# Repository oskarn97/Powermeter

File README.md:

# Powermeter
8-phase induction power meter 16A / 230V

In order to measure the power consumption in each of my rooms, I've designed this induction-based 8 phase power meter, that can be installed in your electricity box next to your breakers.

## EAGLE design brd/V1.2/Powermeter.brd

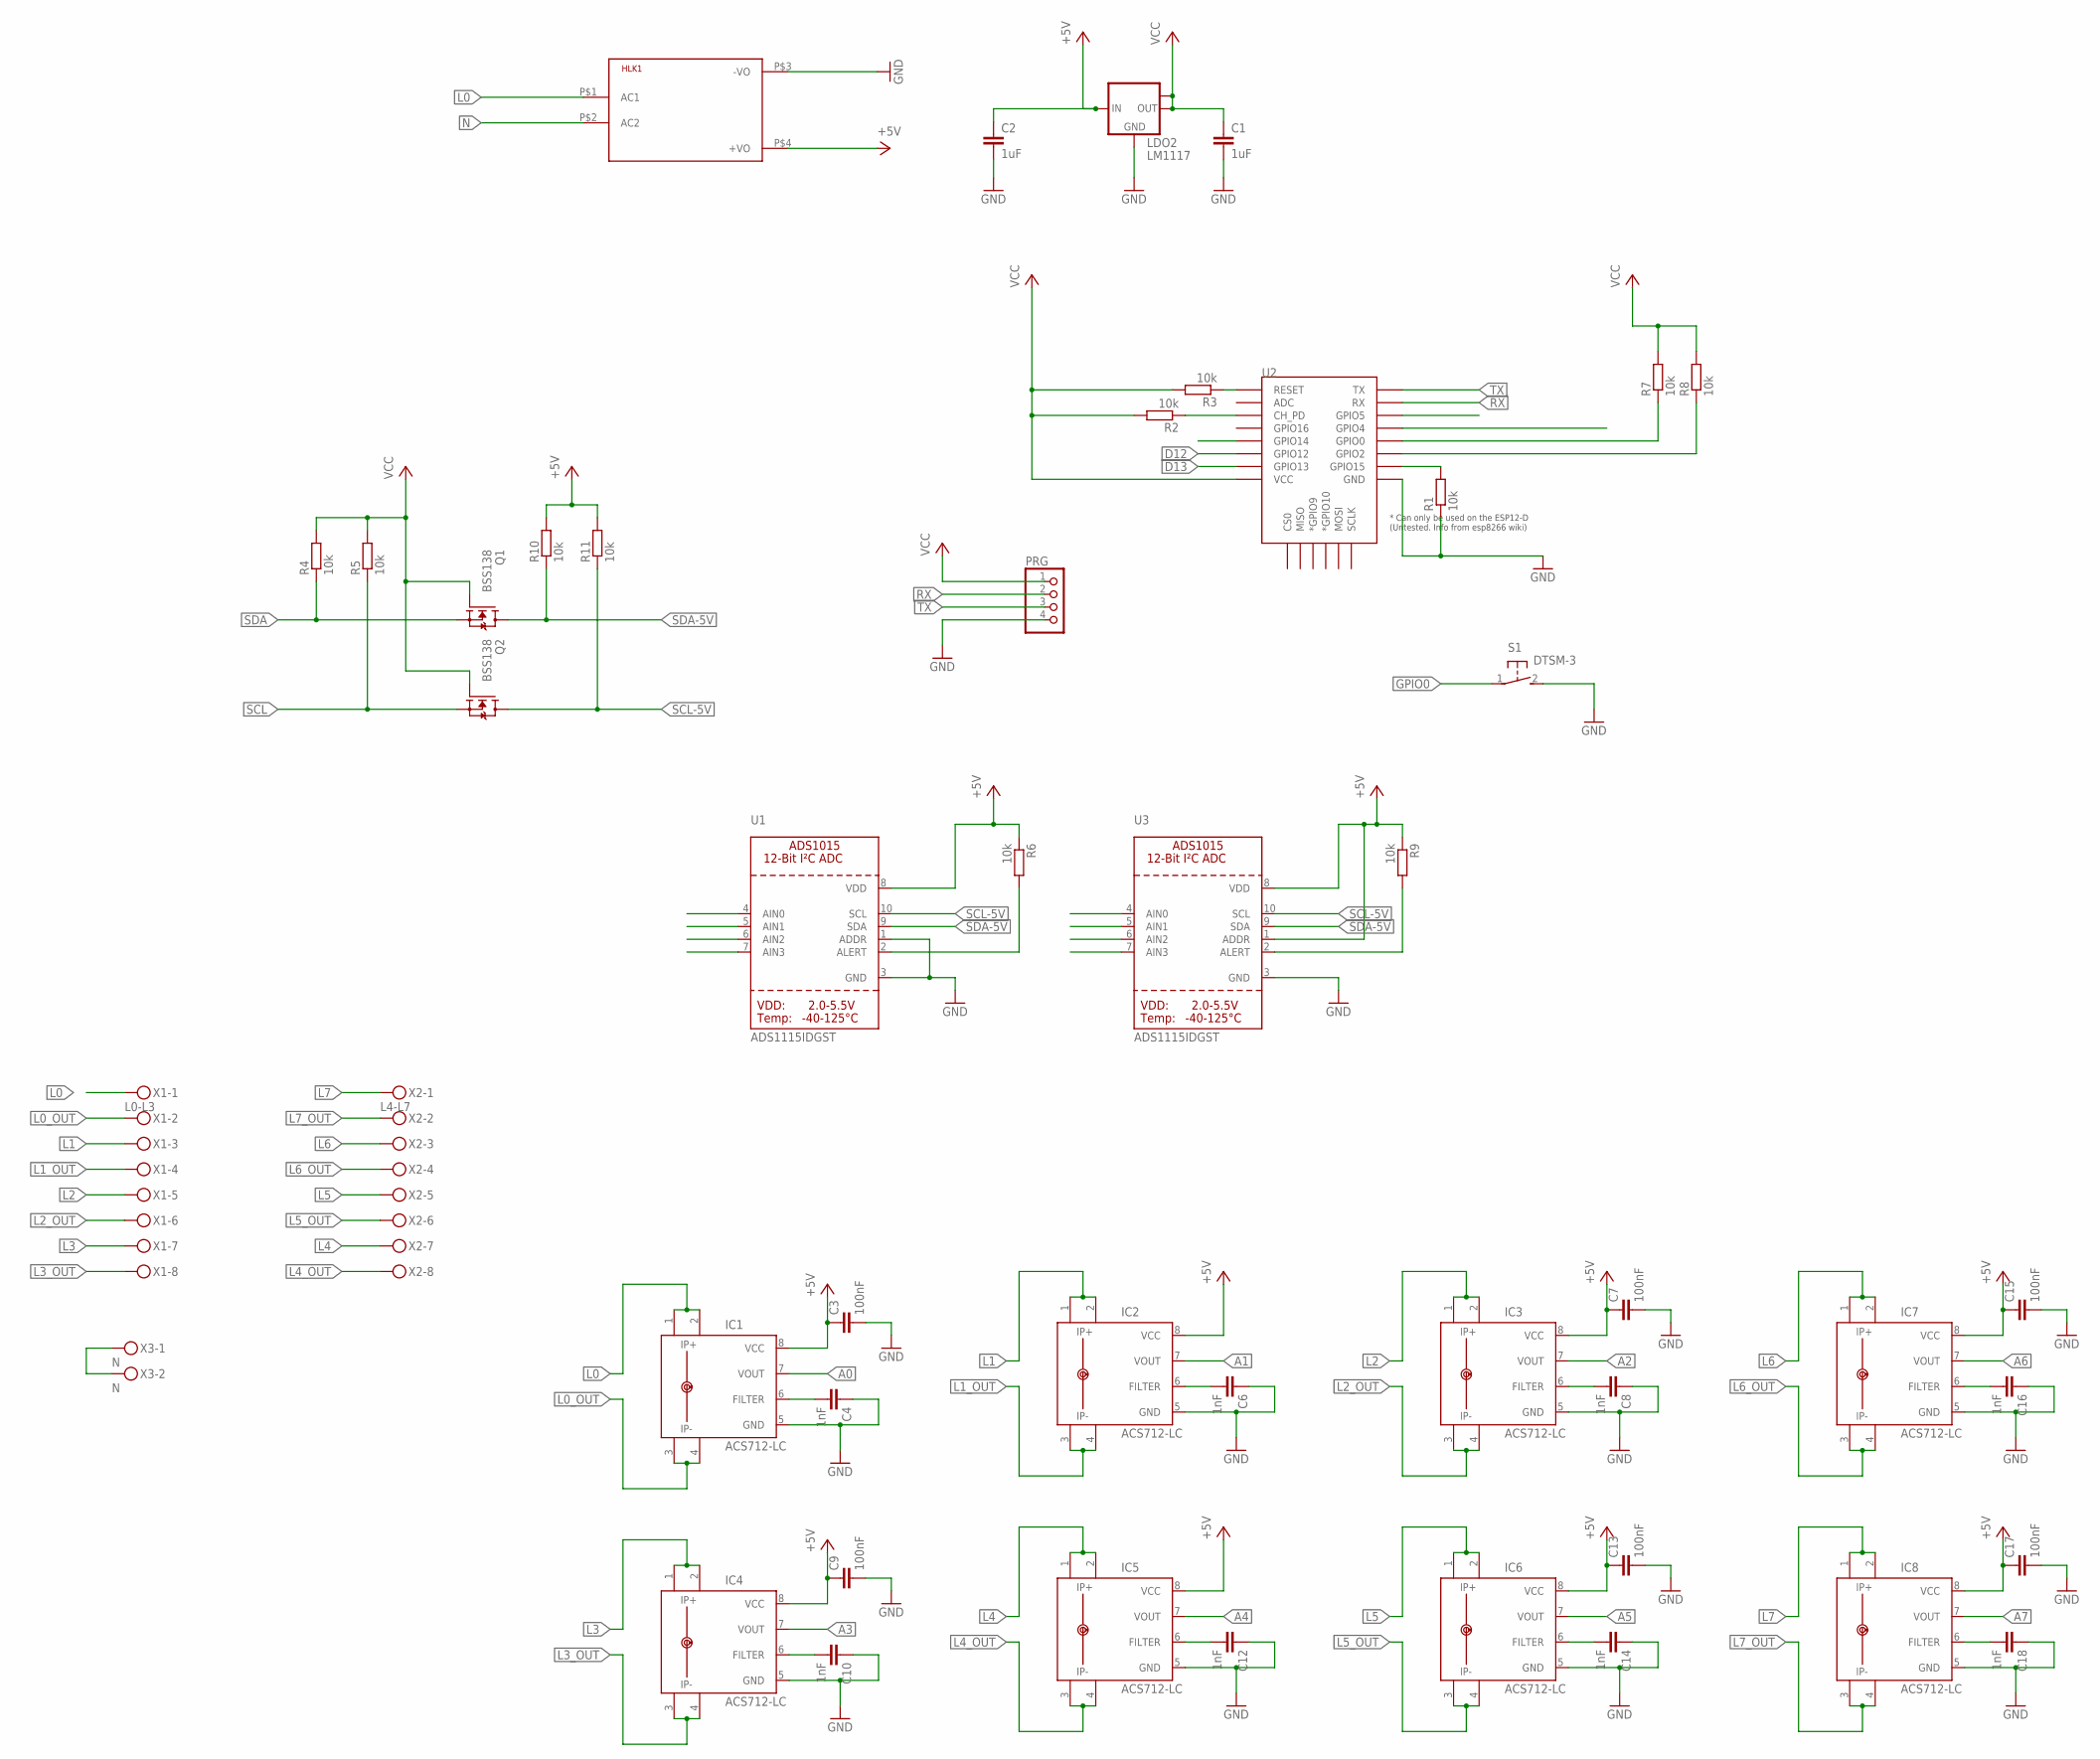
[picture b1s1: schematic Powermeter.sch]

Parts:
C1, C2: 1uF; C0805
C3, C7, C9, C13, C15, C17: 100nF; C0805
C4, C6, C8, C10, C12, C14, C16, C18: 1nF; C0805
HLK1: HLK-PM013W; HLK-PM01
IC1, IC2, IC3, IC4, IC5, IC6, IC7, IC8: ACS712-LC; SOIC8
LDO2: LM1117; SOT223
PRG: PINHD-1X04_2.54-S; 1X04-S
Q1, Q2: BSS138; SOT23
R1, R2, R3, R4, R5, R6, R7, R8, R9, R10, R11: 10k; R0805
S1: DTSM-3
U1, U3: ADS1115IDGST; MSOP10
U2: ESP12ESMD; ESP12E-SMD
X1: L0-L3; MKDSN1,5/8-5,08
X2: L4-L7; MKDSN1,5/8-5,08
X3: N; MKDSN1,5/2-5,08

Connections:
+5V: C2.1, C3.1, C7.1, C9.1, C13.1, C15.1, C17.1, HLK1.P$4 (+VO), IC1.8 (VCC), IC2.8 (VCC), IC3.8 (VCC), IC4.8 (VCC), IC5.8 (VCC), IC6.8 (VCC), IC7.8 (VCC), IC8.8 (VCC), LDO2.3 (IN), R6.1, R9.1, R10.2, R11.2, U1.8 (VDD), U3.1 (ADDR), U3.8 (VDD)
A0: IC1.7 (VOUT), U1.4 (AIN0)
A1: IC2.7 (VOUT), U1.5 (AIN1)
A2: IC3.7 (VOUT), U1.6 (AIN2)
A3: IC4.7 (VOUT), U1.7 (AIN3)
A4: IC5.7 (VOUT), U3.4 (AIN0)
A5: IC6.7 (VOUT), U3.5 (AIN1)
A6: IC7.7 (VOUT), U3.6 (AIN2)
A7: IC8.7 (VOUT), U3.7 (AIN3)
D2: R8.1, U2.GPIO2
D12: U2.GPIO12
D13: U2.GPIO13
D14: U2.GPIO14
GND: C1.2, C2.2, C3.2, C4.1, C6.1, C7.2, C8.1, C9.2, C10.1, C12.1, C13.2, C14.1, C15.2, C16.1, C17.2, C18.1, HLK1.P$3 (-VO), IC1.5 (GND), IC2.5 (GND), IC3.5 (GND), IC4.5 (GND), IC5.5 (GND), IC6.5 (GND), IC7.5 (GND), IC8.5 (GND), LDO2.1 (GND), PRG.4, R1.1, S1.2, U1.1 (ADDR), U1.3 (GND), U2.GND, U3.3 (GND)
GPIO0: R7.1, S1.1, U2.GPIO0
L0: HLK1.P$1 (AC1), IC1.1 (IP+), IC1.2 (IP+1), X1.1
L0_OUT: IC1.3 (IP-), IC1.4 (IP-1), X1.2
L1: IC2.1 (IP+), IC2.2 (IP+1), X1.3
L1_OUT: IC2.3 (IP-), IC2.4 (IP-1), X1.4
L2: IC3.1 (IP+), IC3.2 (IP+1), X1.5
L2_OUT: IC3.3 (IP-), IC3.4 (IP-1), X1.6
L3: IC4.1 (IP+), IC4.2 (IP+1), X1.7
L3_OUT: IC4.3 (IP-), IC4.4 (IP-1), X1.8
L4: IC5.1 (IP+), IC5.2 (IP+1), X2.7
L4_OUT: IC5.3 (IP-), IC5.4 (IP-1), X2.8
L5: IC6.1 (IP+), IC6.2 (IP+1), X2.5
L5_OUT: IC6.3 (IP-), IC6.4 (IP-1), X2.6
L6: IC7.1 (IP+), IC7.2 (IP+1), X2.3
L6_OUT: IC7.3 (IP-), IC7.4 (IP-1), X2.4
L7: IC8.1 (IP+), IC8.2 (IP+1), X2.1
L7_OUT: IC8.3 (IP-), IC8.4 (IP-1), X2.2
N: HLK1.P$2 (AC2), X3.1, X3.2
unnamed: R1.2, U2.GPIO15
unnamed: R6.2, U1.2 (ALERT)
unnamed: R2.1, U2.CH_PD
unnamed: R9.2, U3.2 (ALERT)
unnamed: C4.2, IC1.6 (FILTER)
unnamed: C6.2, IC2.6 (FILTER)
unnamed: C8.2, IC3.6 (FILTER)
unnamed: C10.2, IC4.6 (FILTER)
unnamed: C12.2, IC5.6 (FILTER)
unnamed: C14.2, IC6.6 (FILTER)
unnamed: C16.2, IC7.6 (FILTER)
unnamed: C18.2, IC8.6 (FILTER)
RESET: R3.1, U2.RESET
RX: PRG.2, U2.RXD0 (RX)
SCL: Q2.2 (S), R5.1, U2.GPIO5
SCL-5V: Q2.3 (D), R11.1, U1.10 (SCL), U3.10 (SCL)
SDA: Q1.2 (S), R4.1, U2.GPIO4
SDA-5V: Q1.3 (D), R10.1, U1.9 (SDA), U3.9 (SDA)
TX: PRG.3, U2.TXD0 (TX)
VCC: C1.1, LDO2.2 (OUT), LDO2.TAB (OUT1), PRG.1, Q1.1 (G), Q2.1 (G), R2.2, R3.2, R4.2, R5.2, R7.2, R8.2, U2.VCC

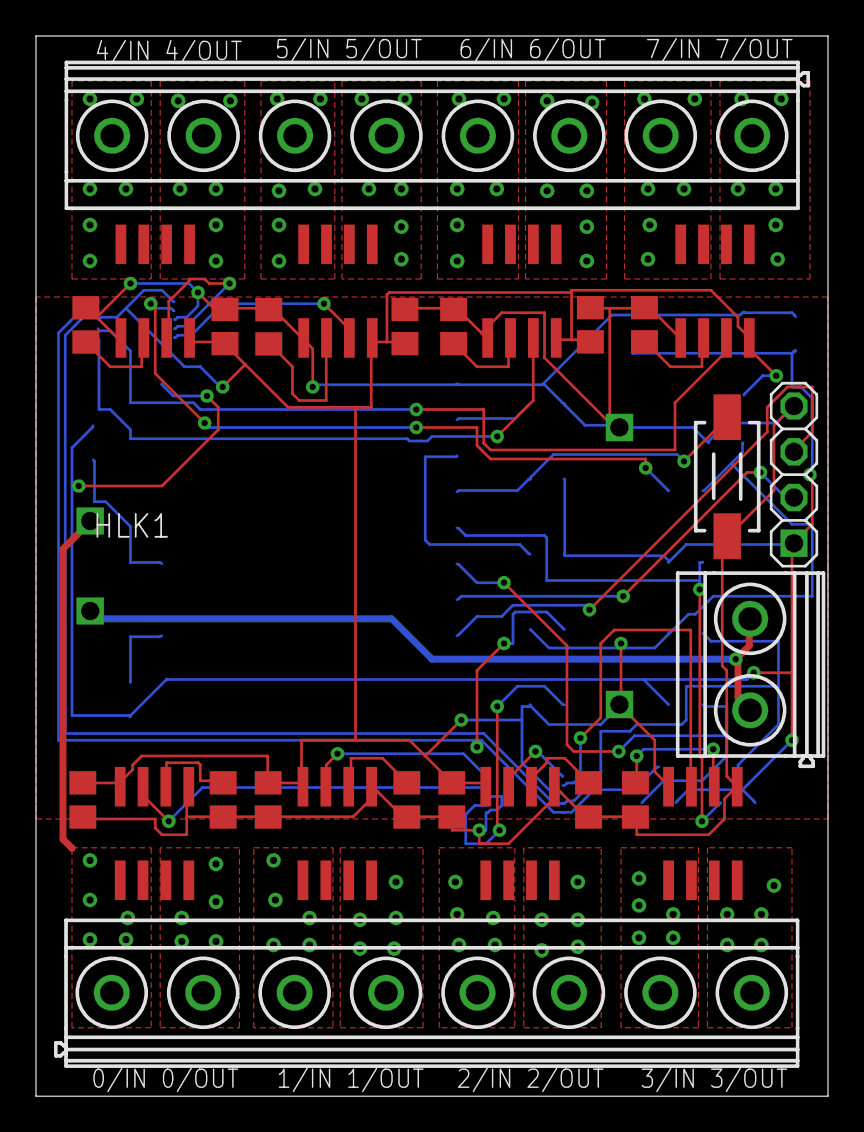
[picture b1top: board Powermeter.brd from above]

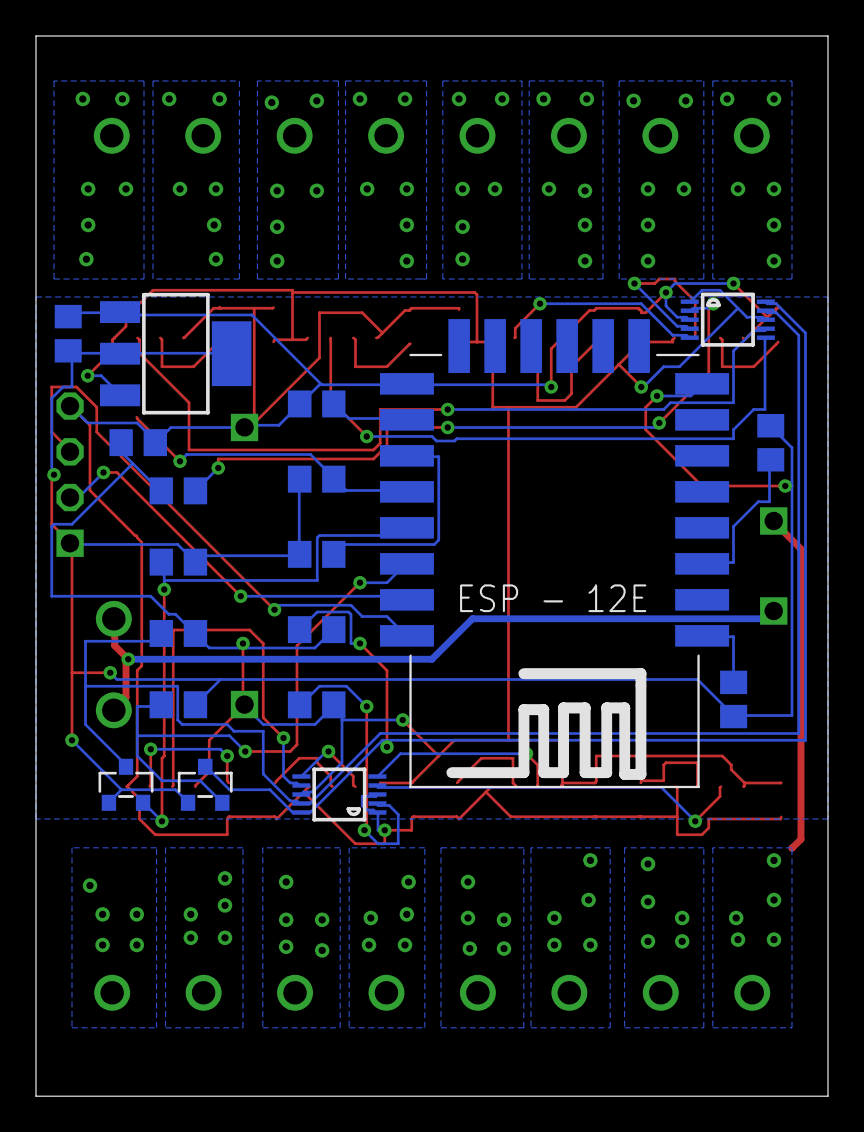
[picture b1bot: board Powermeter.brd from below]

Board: 2 copper layers, 44.0 x 58.9 mm, 47 parts (19 on the bottom side), 49 nets.

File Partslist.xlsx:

Powermeter
Qty | Value | Device | Package | Parts | Description
1 |  | ESP12ESMD | ESP12E-SMD | U2 | ESP12E Module
1 |  | PINHD-1X04_2.54-S | 1X04-S | PRG | Programming Pin Header
6 | 100nF | C-EUC0805 | C0805 | C3, C7, C9, C13, C15, C17 | CAPACITOR
11 | 10k | R-EU_R0805 | R0805 | R1, R2, R3, R4, R5, R6, R7, R8, R9, R10, R11 | RESISTOR
8 | 1nF | C-EUC0805 | C0805 | C4, C6, C8, C10, C12, C14, C16, C18 | CAPACITOR
2 | 1uF | C-EUC0805 | C0805 | C1, C2 | CAPACITOR
8 | ACS712-20A | ACS712-20A | SOIC8 | IC1, IC2, IC3, IC4, IC5, IC6, IC7, IC8 | 20A Induction current sensor
2 | ADS1015 | ADC_ADS1015 | MSOP10 | U1, U3 | ADS1015 - 12-bit 4-Channel I2C ADC with Internal PGA
2 | BSS138 | BSS138 | SOT23 | Q1, Q2 | BSS138 N-Channel Logic Level Enhancement Mode Field Effect Transistor
1 | DTSM-3 | DTSM-3 | DTSM-3 | S1 | Programming switch
1 | HLK-PM01 5V | HLK-PM01 | HLK-PM01 | HLK1 | Hi-Link Power Supply
1 | L0-L3 | MKDSN1,5/8-5,08 | MKDSN1,5/8-5,08 | X1 | MKDSN 1,5/ 8-5,08 Printklemme
1 | L4-L7 | MKDSN1,5/8-5,08 | MKDSN1,5/8-5,08 | X2 | MKDSN 1,5/ 8-5,08 Printklemme
1 | N | MKDSN1,5/2-5,08 | MKDSN1,5/2-5,08 | X3 | MKDSN 1,5/ 2-5,08 Printklemme
1 | LM1117 | LM1117MPX-3.3 | SOT223 | LDO2 | 3.3V DC-DC

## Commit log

2019-03-13 inital commit
